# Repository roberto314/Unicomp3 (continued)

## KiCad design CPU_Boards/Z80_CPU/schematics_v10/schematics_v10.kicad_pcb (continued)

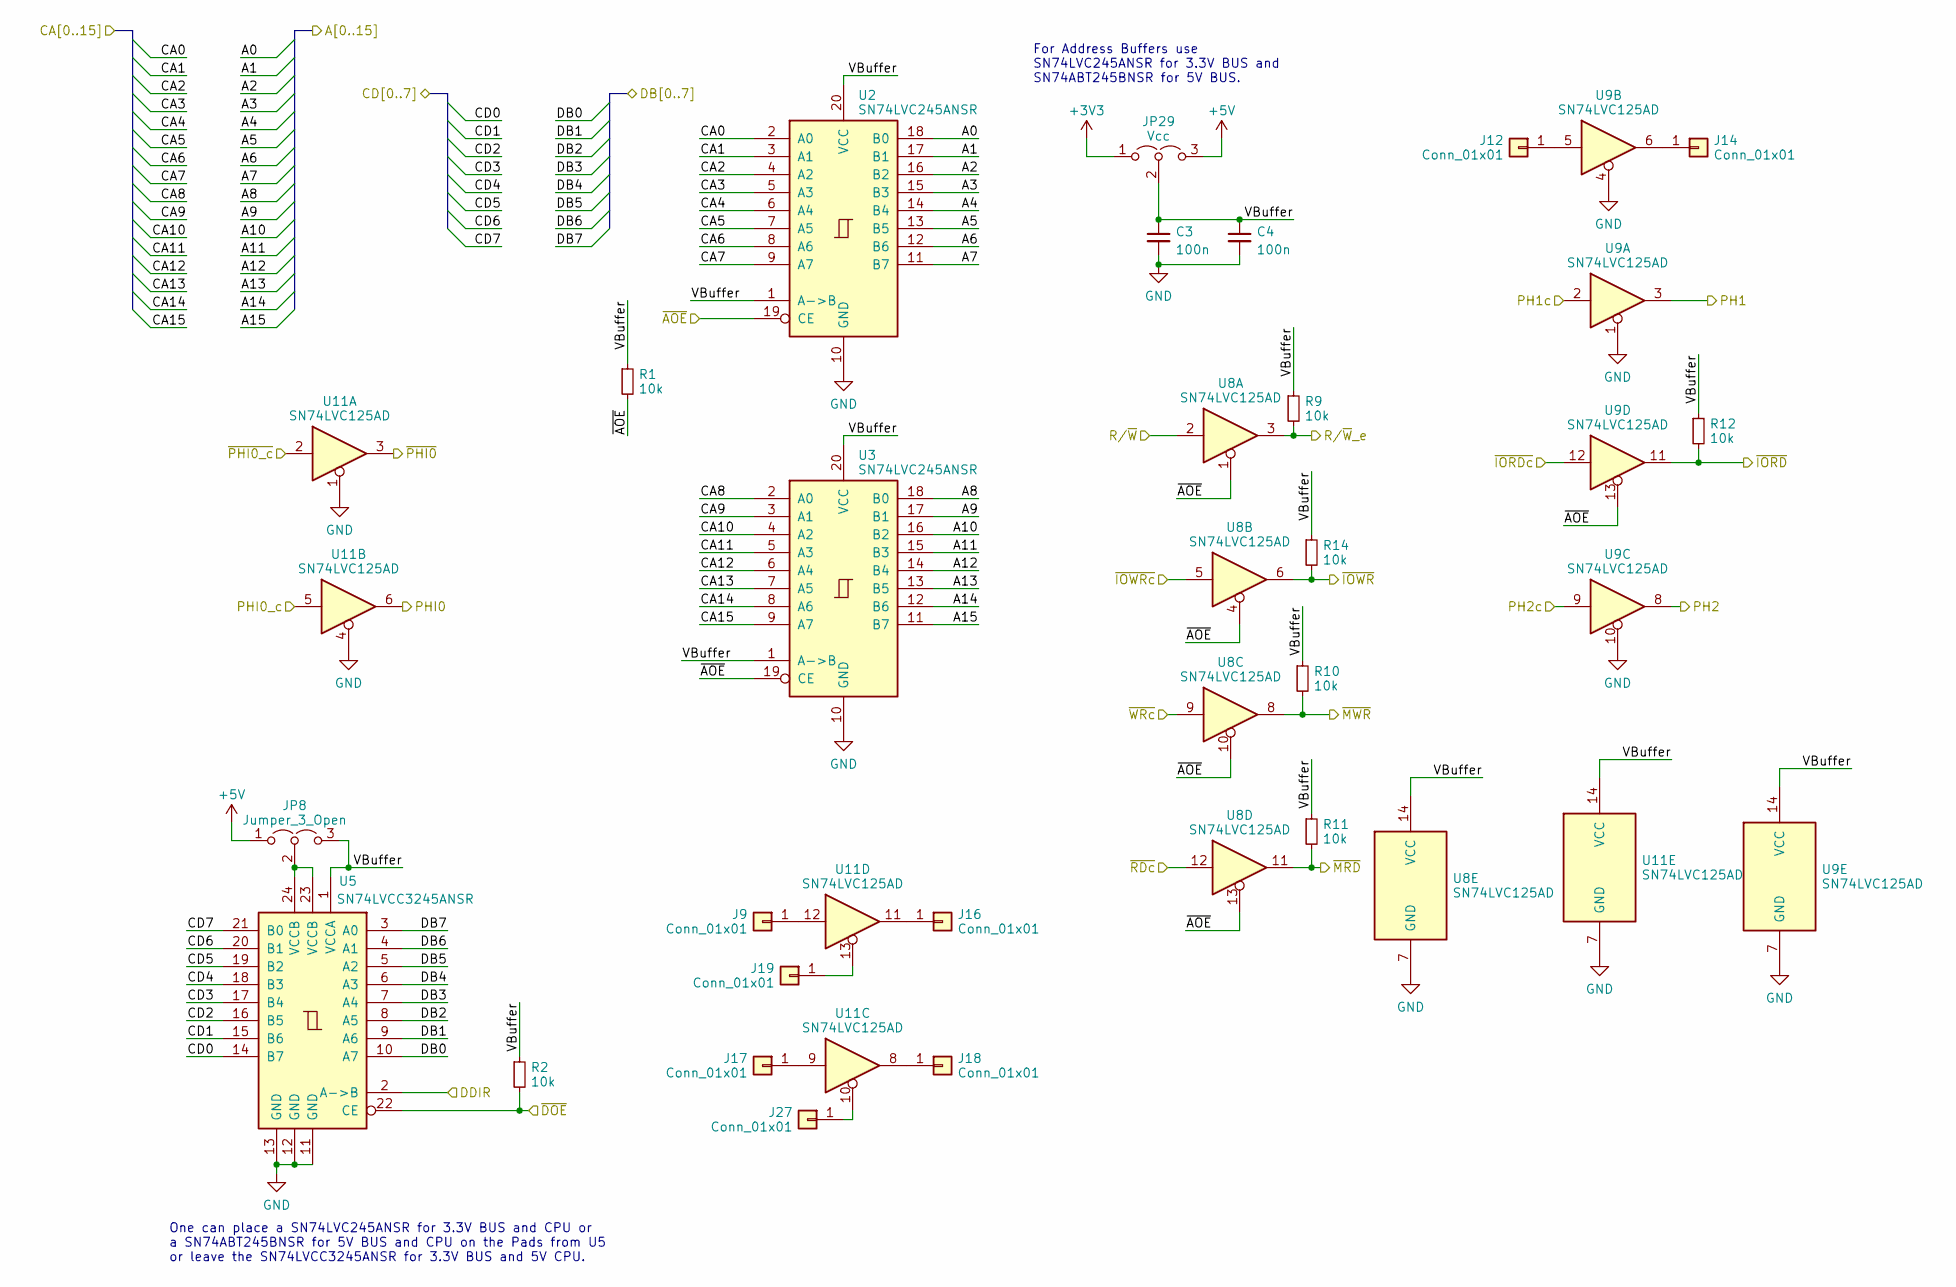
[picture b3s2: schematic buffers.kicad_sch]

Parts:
C3, C4: 100n; C_1206_3216Metric
J9, J12, J14, J16, J17, J18, J19, J27: Conn_01x01; PinHeader_1x01_P1.27mm_Vertical
JP8: Jumper_3_Open; SolderJumper-3_P1.3mm_Open_Pad1.0x1.5mm_NumberLabels
JP29: Vcc; SolderJumper-3_P1.3mm_Open_RoundedPad1.0x1.5mm_NumberLabels
R1, R2, R9, R10, R11, R12, R14: 10k; R_1206_3216Metric_Pad1.30x1.75mm_HandSolder
U2, U3: SN74LVC245ANSR; SO-20_5.3x12.6mm_P1.27mm
U5: SN74LVCC3245ANSR; SO-24_5.3x15mm_P1.27mm
U8, U9, U11: SN74LVC125AD; SOIC-14_3.9x8.7mm_P1.27mm

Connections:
+3V3: JP29.1 (A); also elsewhere on the board
+5V: JP8.1 (A), JP29.3 (B); also elsewhere on the board
/A0: U2.18 (B0); also elsewhere on the board
/A1: U2.17 (B1); also elsewhere on the board
/A2: U2.16 (B2); also elsewhere on the board
/A3: U2.15 (B3); also elsewhere on the board
/A4: U2.14 (B4); also elsewhere on the board
/A5: U2.13 (B5); also elsewhere on the board
/A6: U2.12 (B6); also elsewhere on the board
/A7: U2.11 (B7); also elsewhere on the board
/A8: U3.18 (B0); also elsewhere on the board
/A9: U3.17 (B1); also elsewhere on the board
/A10: U3.16 (B2); also elsewhere on the board
/A11: U3.15 (B3); also elsewhere on the board
/A12: U3.14 (B4); also elsewhere on the board
/A13: U3.13 (B5); also elsewhere on the board
/A14: U3.12 (B6); also elsewhere on the board
/A15: U3.11 (B7); also elsewhere on the board
/Buffers/R/~W: U8.2; also elsewhere on the board
/Buffers/VBuffer: C3.1, C4.1, JP8.3 (B), JP29.2 (C), R1.1, R2.1, R9.1, R10.1, R11.1, R12.1, R14.1, U2.1 (A->B), U2.20 (VCC), U3.1 (A->B), U3.20 (VCC), U5.1 (VCCA), U8.14 (VCC), U9.14 (VCC), U11.14 (VCC)
/CA0: U2.2 (A0); also elsewhere on the board
/CA1: U2.3 (A1); also elsewhere on the board
/CA2: U2.4 (A2); also elsewhere on the board
/CA3: U2.5 (A3); also elsewhere on the board
/CA4: U2.6 (A4); also elsewhere on the board
/CA5: U2.7 (A5); also elsewhere on the board
/CA6: U2.8 (A6); also elsewhere on the board
/CA7: U2.9 (A7); also elsewhere on the board
/CA8: U3.2 (A0); also elsewhere on the board
/CA9: U3.3 (A1); also elsewhere on the board
/CA10: U3.4 (A2); also elsewhere on the board
/CA11: U3.5 (A3); also elsewhere on the board
/CA12: U3.6 (A4); also elsewhere on the board
/CA13: U3.7 (A5); also elsewhere on the board
/CA14: U3.8 (A6); also elsewhere on the board
/CA15: U3.9 (A7); also elsewhere on the board
/CD0: U5.14 (B7); also elsewhere on the board
/CD1: U5.15 (B6); also elsewhere on the board
/CD2: U5.16 (B5); also elsewhere on the board
/CD3: U5.17 (B4); also elsewhere on the board
/CD4: U5.18 (B3); also elsewhere on the board
/CD5: U5.19 (B2); also elsewhere on the board
/CD6: U5.20 (B1); also elsewhere on the board
/CD7: U5.21 (B0); also elsewhere on the board
/DB0: U5.10 (A7); also elsewhere on the board
/DB1: U5.9 (A6); also elsewhere on the board
/DB2: U5.8 (A5); also elsewhere on the board
/DB3: U5.7 (A4); also elsewhere on the board
/DB4: U5.6 (A3); also elsewhere on the board
/DB5: U5.5 (A2); also elsewhere on the board
/DB6: U5.4 (A1); also elsewhere on the board
/DB7: U5.3 (A0); also elsewhere on the board
/DDIR: U5.2 (A->B); also elsewhere on the board
/PH1: U9.3; also elsewhere on the board
/PH1c: U9.2; also elsewhere on the board
/PH2: U9.8; also elsewhere on the board
/PH2c: U9.9; also elsewhere on the board
/PHI0: U11.6; also elsewhere on the board
/PHI0_c: U11.5; also elsewhere on the board
/R/~W_e: R9.2, U8.3; also elsewhere on the board
/ZZ3: U11.2; also elsewhere on the board
/ZZ5: R1.2, U2.19 (CE), U3.19 (CE), U8.1, U8.4, U8.10, U8.13, U9.13; also elsewhere on the board
/ZZ6: R2.2, U5.22 (CE); also elsewhere on the board
/ZZ8: U8.9; also elsewhere on the board
/ZZ12: U8.12; also elsewhere on the board
/ZZ13: U9.12; also elsewhere on the board
/ZZ16: U8.5; also elsewhere on the board
/~IORD: R12.2, U9.11; also elsewhere on the board
/~IOWR: R14.2, U8.6; also elsewhere on the board
/~MRD: R11.2, U8.11; also elsewhere on the board
/~MWR: R10.2, U8.8; also elsewhere on the board
/~PHI0: U11.3; also elsewhere on the board
GND: C3.2, C4.2, U2.10 (GND), U3.10 (GND), U5.11 (GND), U5.12 (GND), U5.13 (GND), U8.7 (GND), U9.1, U9.4, U9.7 (GND), U9.10, U11.1, U11.4, U11.7 (GND); also elsewhere on the board
unnamed: J9.1, U11.12
unnamed: J12.1, U9.5
unnamed: J14.1, U9.6
unnamed: J16.1, U11.11
unnamed: J17.1, U11.9
unnamed: J18.1, U11.8
unnamed: J19.1, U11.13
unnamed: J27.1, U11.10
unnamed: JP8.2 (C), U5.23 (VCCB), U5.24 (VCCB)

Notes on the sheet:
One can place a SN74LVC245ANSR for 3.3V BUS and CPU or a SN74ABT245BNSR for 5V BUS and CPU on the Pads from U5 or leave the SN74LVCC3245ANSR for 3.3V BUS and 5V CPU.
For Address Buffers use SN74LVC245ANSR for 3.3V BUS and SN74ABT245BNSR for 5V BUS.

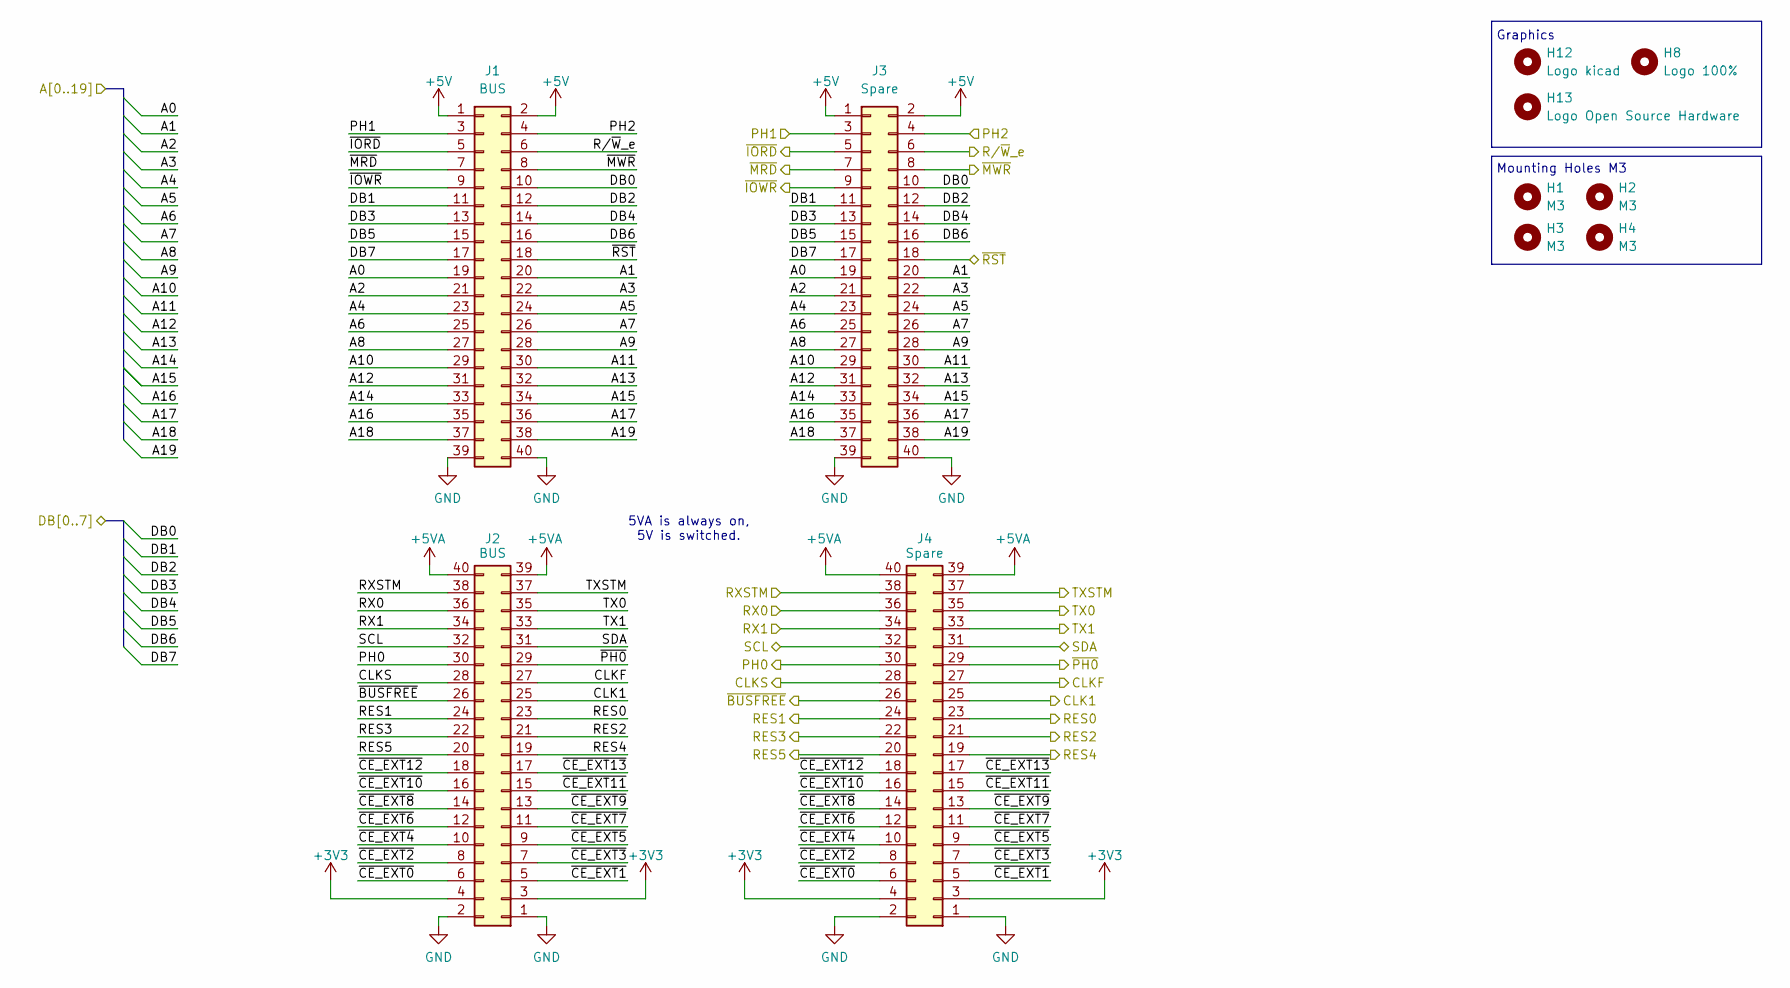
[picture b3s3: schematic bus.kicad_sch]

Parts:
H1, H2, H3, H4: M3; MountingHole_3.2mm_M3
H8: Logo 100%; Logo_100ProzentOffner_10x2.7mm
H12: Logo kicad; KiCad-Logo2_6mm_SilkScreen
H13: Logo Open Source Hardware; OSHW-Logo2_7.3x6mm_SilkScreen
J1, J2: BUS; PinSocket_2x20_P2.54mm_Vertical
J3, J4: Spare; PinSocket_2x20_P2.54mm_Vertical

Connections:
+3V3: J2.3, J2.4, J4.3, J4.4; also elsewhere on the board
+5V: J1.1, J1.2, J3.1, J3.2; also elsewhere on the board
+5VA: J2.39, J2.40, J4.39, J4.40; also elsewhere on the board
/A0: J1.19, J3.19; also elsewhere on the board
/A1: J1.20, J3.20; also elsewhere on the board
/A2: J1.21, J3.21; also elsewhere on the board
/A3: J1.22, J3.22; also elsewhere on the board
/A4: J1.23, J3.23; also elsewhere on the board
/A5: J1.24, J3.24; also elsewhere on the board
/A6: J1.25, J3.25; also elsewhere on the board
/A7: J1.26, J3.26; also elsewhere on the board
/A8: J1.27, J3.27; also elsewhere on the board
/A9: J1.28, J3.28; also elsewhere on the board
/A10: J1.29, J3.29; also elsewhere on the board
/A11: J1.30, J3.30; also elsewhere on the board
/A12: J1.31, J3.31; also elsewhere on the board
/A13: J1.32, J3.32; also elsewhere on the board
/A14: J1.33, J3.33; also elsewhere on the board
/A15: J1.34, J3.34; also elsewhere on the board
/Bus/A16: J1.35, J3.35
/Bus/A17: J1.36, J3.36
/Bus/A18: J1.37, J3.37
/Bus/A19: J1.38, J3.38
/Bus/CLK1: J2.25, J4.25
/Bus/RES2: J2.21, J4.21
/Bus/RES3: J2.22, J4.22
/Bus/RES4: J2.19, J4.19
/Bus/RES5: J2.20, J4.20
/Bus/RX0: J2.36, J4.36
/Bus/RX1: J2.34, J4.34
/Bus/RXSTM: J2.38, J4.38
/Bus/SCL: J2.32, J4.32
/Bus/SDA: J2.31, J4.31
/Bus/TX0: J2.35, J4.35
/Bus/TX1: J2.33, J4.33
/Bus/TXSTM: J2.37, J4.37
/Bus/~CE_EXT0: J2.6, J4.6
/Bus/~CE_EXT1: J2.5, J4.5
/Bus/~CE_EXT2: J2.8, J4.8
/Bus/~CE_EXT3: J2.7, J4.7
/Bus/~CE_EXT4: J2.10, J4.10
/Bus/~CE_EXT5: J2.9, J4.9
/Bus/~CE_EXT6: J2.12, J4.12
/Bus/~CE_EXT7: J2.11, J4.11
/Bus/~CE_EXT8: J2.14, J4.14
/Bus/~CE_EXT9: J2.13, J4.13
/Bus/~CE_EXT10: J2.16, J4.16
/Bus/~CE_EXT11: J2.15, J4.15
/Bus/~CE_EXT12: J2.18, J4.18
/Bus/~CE_EXT13: J2.17, J4.17
/CLKF: J2.27, J4.27; also elsewhere on the board
/CLKS: J2.28, J4.28
/DB0: J1.10, J3.10; also elsewhere on the board
/DB1: J1.11, J3.11; also elsewhere on the board
/DB2: J1.12, J3.12; also elsewhere on the board
/DB3: J1.13, J3.13; also elsewhere on the board
/DB4: J1.14, J3.14; also elsewhere on the board
/DB5: J1.15, J3.15; also elsewhere on the board
/DB6: J1.16, J3.16; also elsewhere on the board
/DB7: J1.17, J3.17; also elsewhere on the board
/PH1: J1.3, J3.3; also elsewhere on the board
/PH2: J1.4, J3.4; also elsewhere on the board
/PHI0: J2.30, J4.30; also elsewhere on the board
/RES0: J2.23, J4.23
/RES1: J2.24, J4.24
/R/~W_e: J1.6, J3.6; also elsewhere on the board
/ZZ43: J2.26, J4.26; also elsewhere on the board
/~IORD: J1.5, J3.5; also elsewhere on the board
/~IOWR: J1.9, J3.9; also elsewhere on the board
/~MRD: J1.7, J3.7; also elsewhere on the board
/~MWR: J1.8, J3.8; also elsewhere on the board
/~PHI0: J2.29, J4.29; also elsewhere on the board
/~RST: J1.18, J3.18; also elsewhere on the board
GND: J1.39, J1.40, J2.1, J2.2, J3.39, J3.40, J4.1, J4.2; also elsewhere on the board

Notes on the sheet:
5VA is always on, 5V is switched.
Graphics
Mounting Holes M3

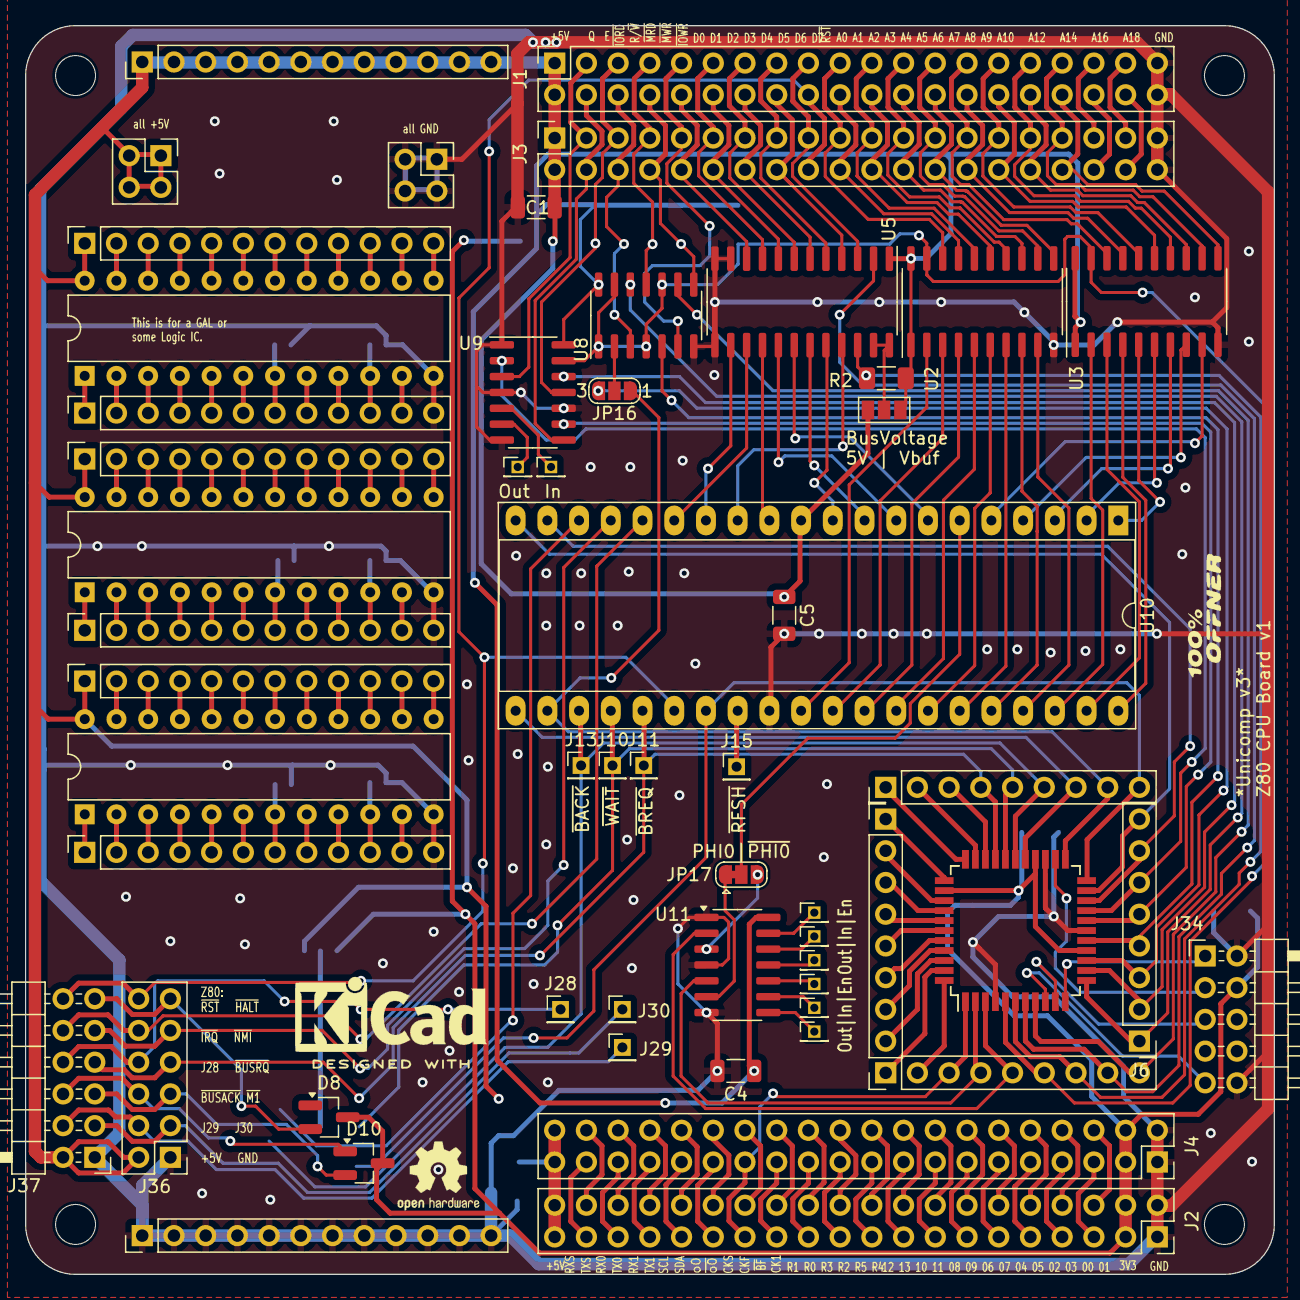
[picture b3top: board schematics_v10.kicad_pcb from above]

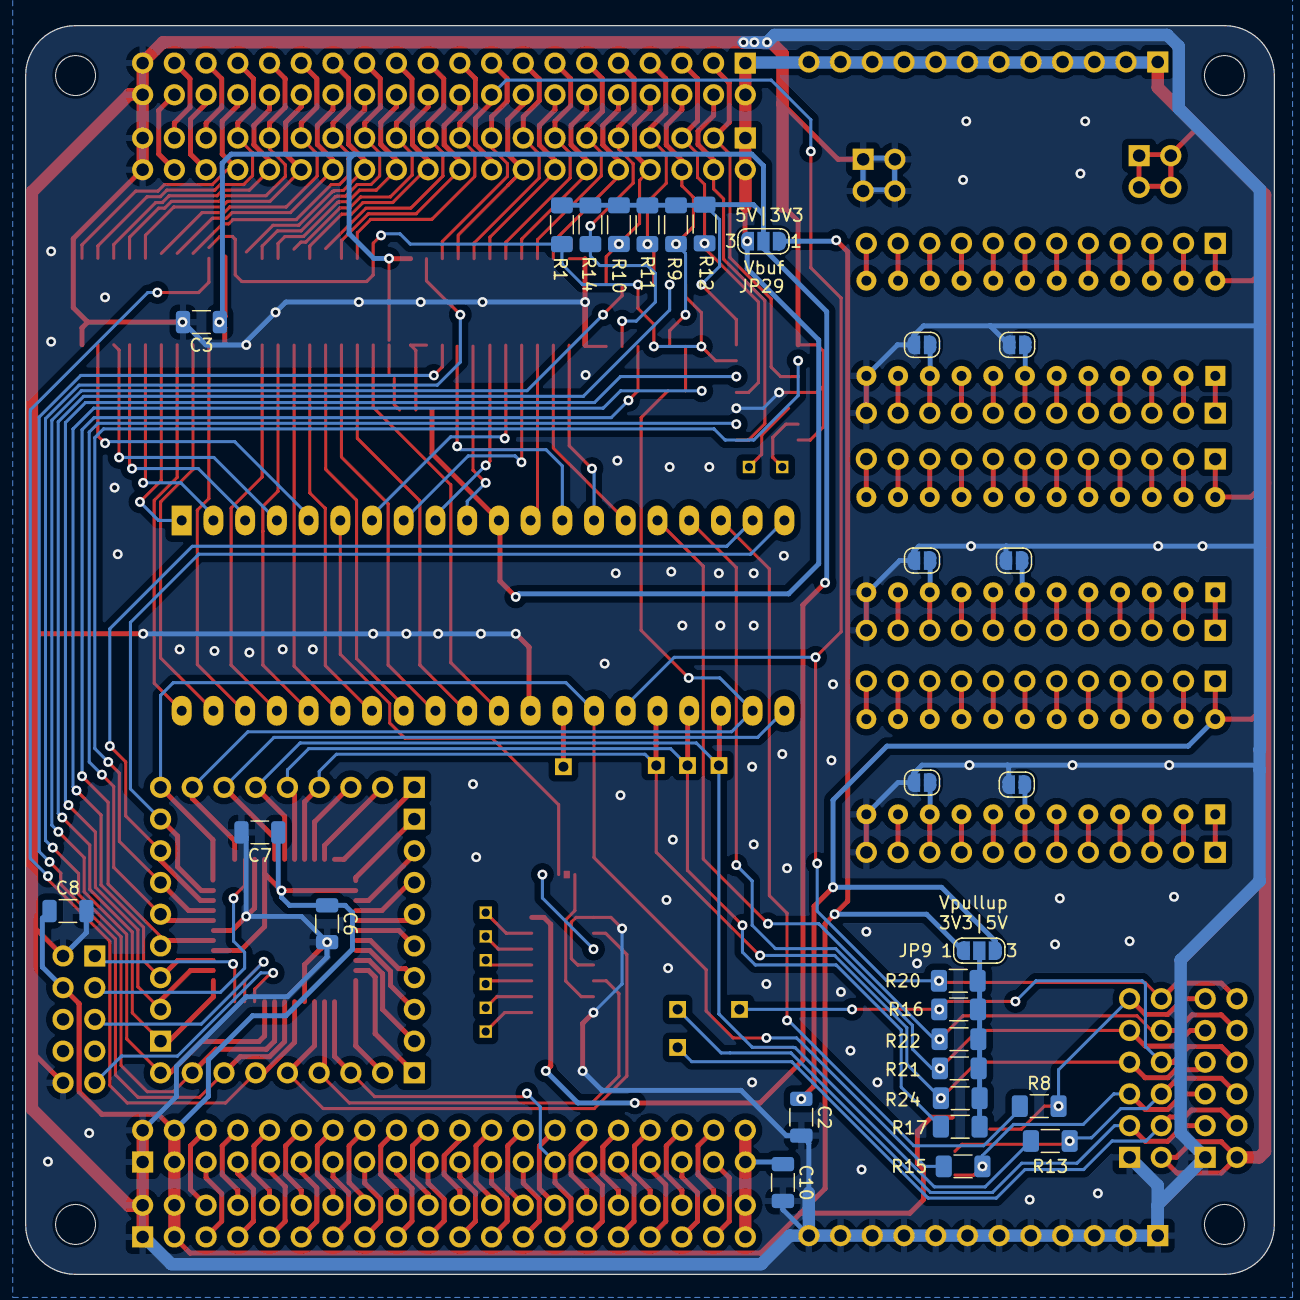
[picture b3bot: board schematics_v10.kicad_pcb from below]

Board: 2 copper layers, 100.0 x 100.0 mm, 92 parts (29 on the bottom side), 223 nets.

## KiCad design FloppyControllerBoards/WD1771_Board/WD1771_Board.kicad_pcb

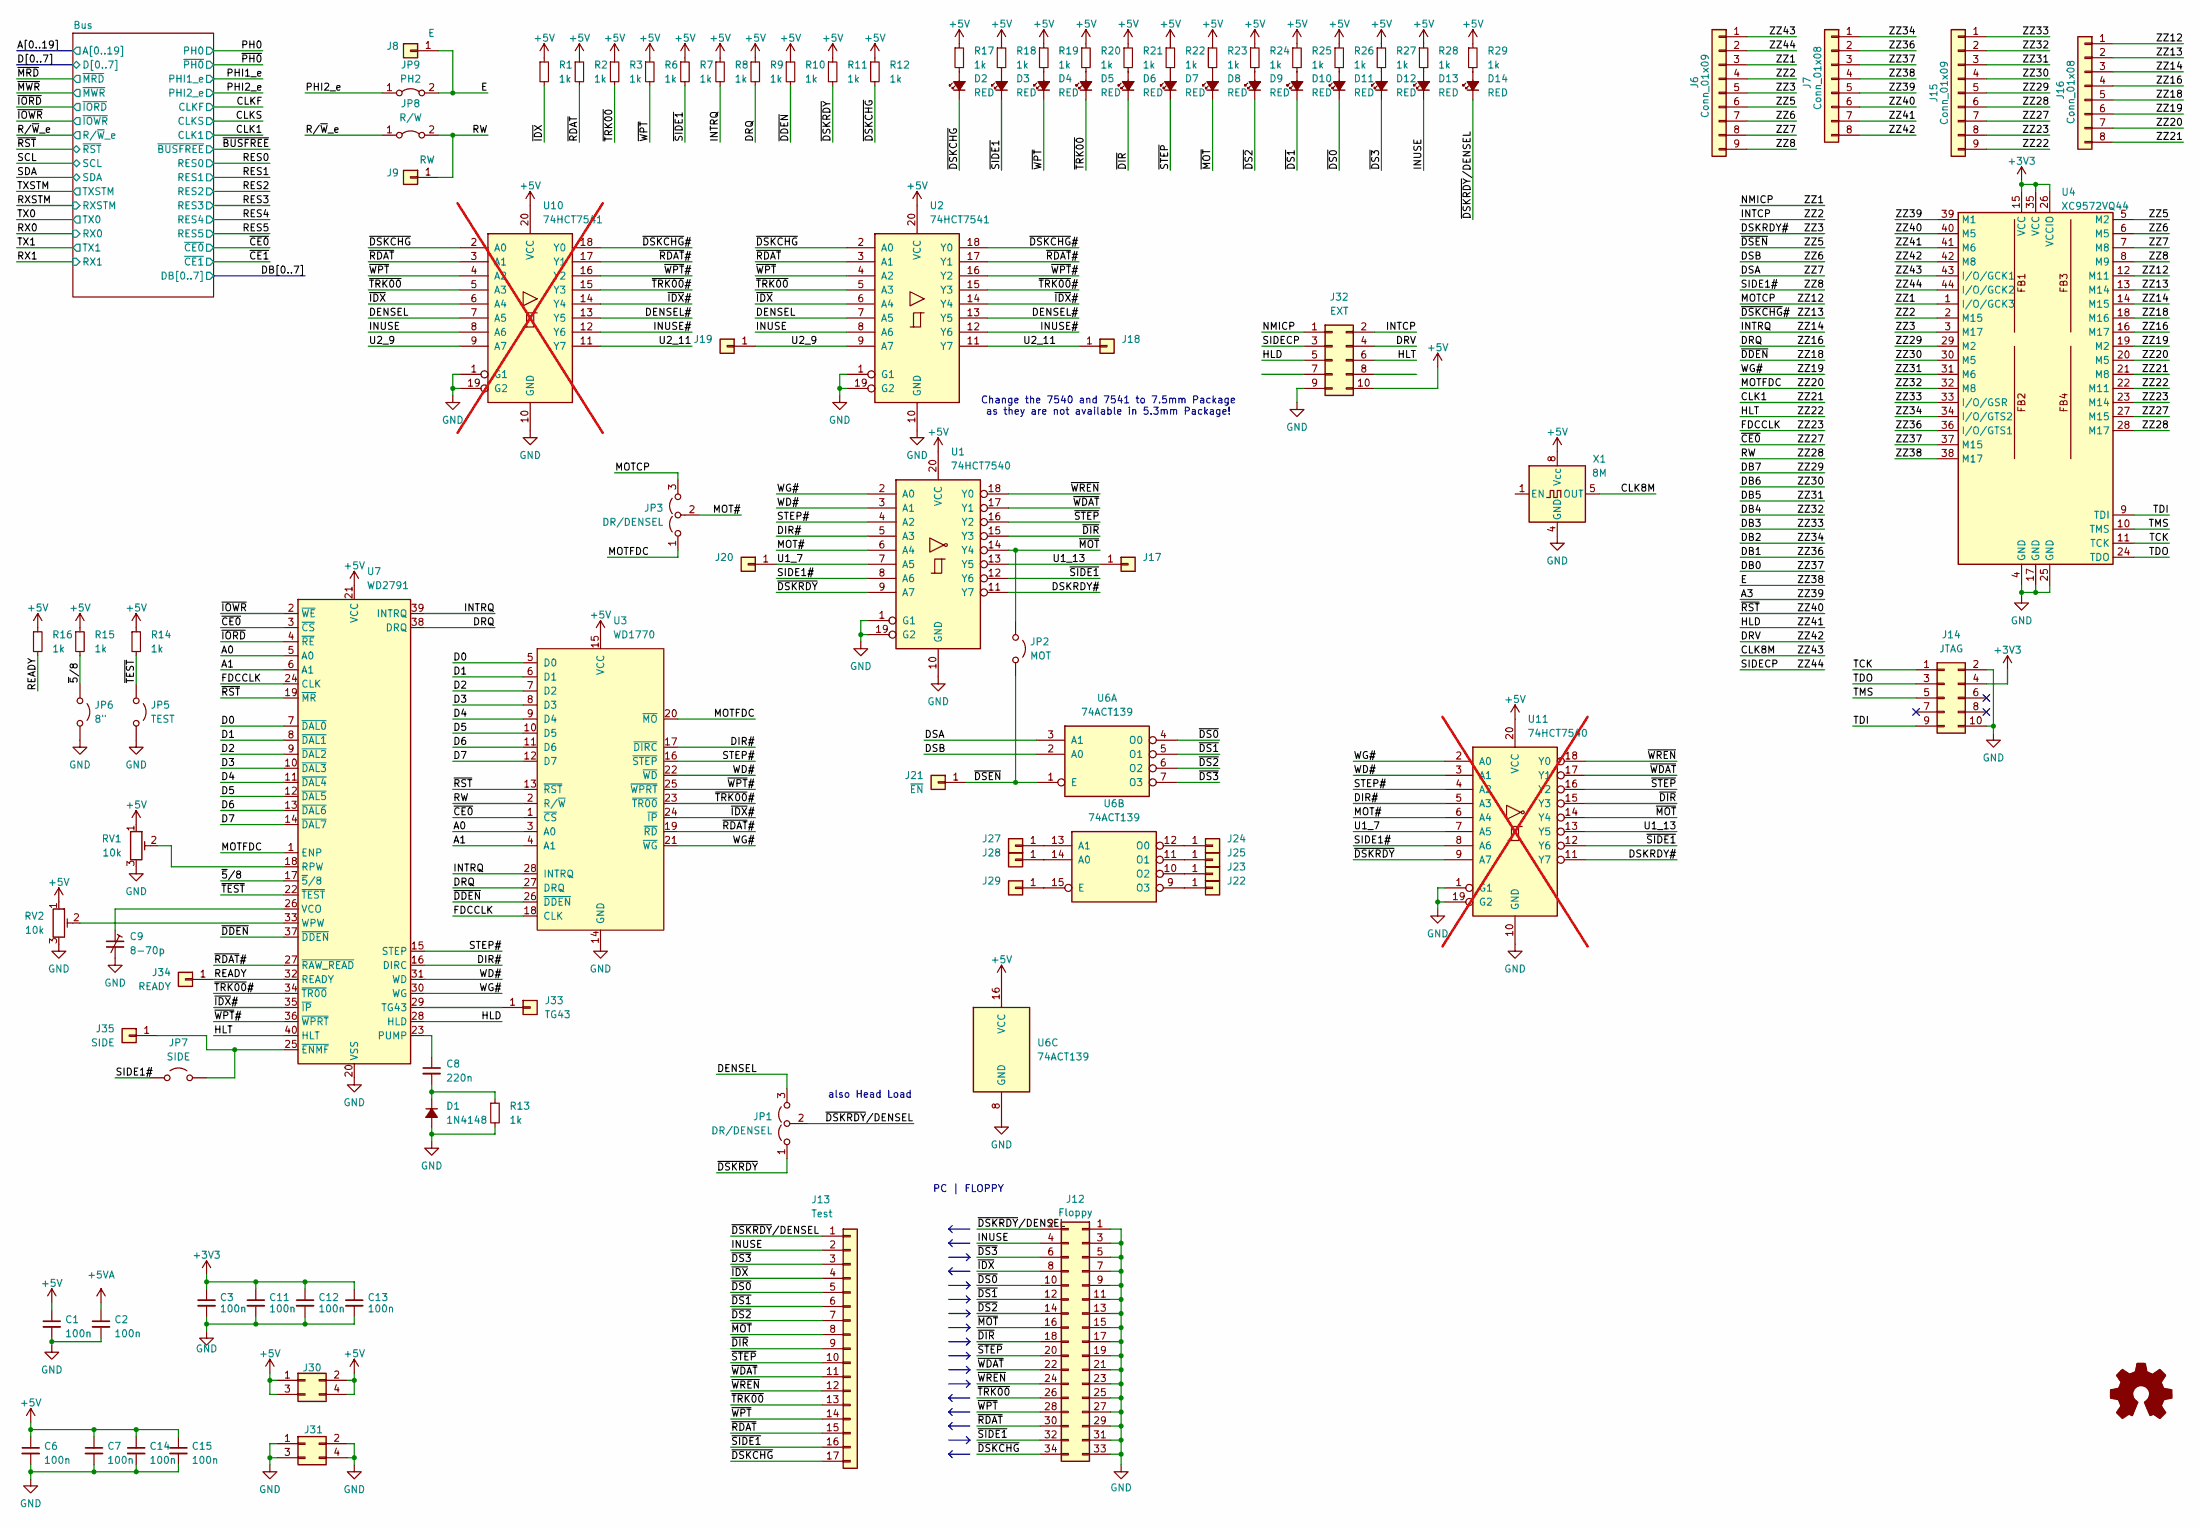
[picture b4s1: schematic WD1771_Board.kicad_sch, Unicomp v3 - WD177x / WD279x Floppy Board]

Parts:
C1, C2, C3, C6, C7, C11, C12, C13, C14, C15: 100n; C_1206_3216Metric
C8: 220n; C_1206_3216Metric
C9: 8-70p; Capacitor_Trim
D1: 1N4148; D_1206_3216Metric_Pad1.42x1.75mm_HandSolder
D2, D3, D4, D5, D6, D7, D8, D9, D10, D11, D12, D13, D14: RED; LED_1206_3216Metric_Pad1.42x1.75mm_HandSolder
J6, J15: Conn_01x09; PinHeader_1x09_P2.54mm_Vertical
J7, J16: Conn_01x08; PinHeader_1x08_P2.54mm_Vertical
J8: E; PinHeader_1x01_P2.00mm_Vertical
J9: RW; PinHeader_1x01_P2.00mm_Vertical
J12: Floppy; PinHeader_2x17_P2.54mm_Horizontal
J13: Test; PinSocket_1x17_P2.54mm_Vertical
J14: JTAG; PinHeader_2x05_P2.54mm_Horizontal
J17, J18, J19, J20, J22, J23, J24, J25, J27, J28, J29: Conn_01x01; PinHeader_1x01_P1.27mm_Vertical
J21: ~{EN}; PinHeader_1x01_P1.27mm_Vertical
J30, J31: Conn_02x02_Odd_Even; PinSocket_2x02_P2.54mm_Vertical
J32: EXT; PinHeader_2x05_P2.54mm_Horizontal
J33: TG43; PinHeader_1x01_P1.27mm_Vertical
J34: READY; PinHeader_1x01_P1.27mm_Vertical
J35: SIDE; PinHeader_1x01_P1.27mm_Vertical
JP1, JP3: DR/DENSEL; PinHeader_1x03_P2.54mm_Vertical
JP2: MOT; SolderJumper-2_P1.3mm_Open_RoundedPad1.0x1.5mm
JP5: TEST; SolderJumper-2_P1.3mm_Open_RoundedPad1.0x1.5mm
JP6: 8"; PinHeader_1x02_P2.54mm_Vertical
JP7: SIDE; SolderJumper-2_P1.3mm_Open_RoundedPad1.0x1.5mm
JP8: R/W; SolderJumper-2_P1.3mm_Bridged_RoundedPad1.0x1.5mm
JP9: PH2; SolderJumper-2_P1.3mm_Bridged_RoundedPad1.0x1.5mm
R1, R2, R3, R6, R7, R8, R9, R10, R11, R12, R13, R14, R15, R16, R17, R18, R19, R20, R21, R22, R23, R24, R25, R26, R27, R28, R29: 1k; R_1206_3216Metric_Pad1.30x1.75mm_HandSolder
RV1, RV2: 10k; Potentiometer_Vishay_T73XW_Horizontal
U1: 74HCT7540; SO-20_5.3x12.6mm_P1.27mm
U2: 74HCT7541; SO-20_5.3x12.6mm_P1.27mm
U3: WD1770; DIP-28_W15.24mm_Socket
U4: XC9572VQ44; TQFP-44_10x10mm_P0.8mm
U6: 74ACT139; SOIC-16_3.9x9.9mm_P1.27mm
U7: WD2791; DIP-40_W15.24mm
U10: 74HCT7541; SO-20_12.8x7.5mm_P1.27mm; not fitted
U11: 74HCT7540; SO-20_12.8x7.5mm_P1.27mm; not fitted
X1: 8M; Oscillator_DIP-8

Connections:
+3V3: C3.1, C11.1, C12.1, C13.1, J14.4, U4.15 (VCC), U4.26 (VCCIO), U4.35 (VCC); also elsewhere on the board
+5V: C1.1, C6.1, C7.1, C14.1, C15.1, J30.1, J30.2, J30.3, J30.4, J32.10, R1.1, R2.1, R3.1, R6.1, R7.1, R8.1, R9.1, R10.1, R11.1, R12.1, R14.1, R15.1, R16.1, R17.1, R18.1, R19.1, R20.1, R21.1, R22.1, R23.1, R24.1, R25.1, R26.1, R27.1, R28.1, R29.1, RV1.1, RV2.1, U1.20 (VCC), U2.20 (VCC), U3.15 (VCC), U6.16 (VCC), U7.21 (VCC), U10.20 (VCC), U11.20 (VCC), X1.8 (Vcc); also elsewhere on the board
+5VA: C2.1; also elsewhere on the board
/A0: U3.3 (A0), U7.5 (A0); also elsewhere on the board
/A1: U3.4 (A1), U7.6 (A1); also elsewhere on the board
/A3: J7.5, U4.39 (M1); also elsewhere on the board
/CLK1: J16.8, U4.21 (M8); also elsewhere on the board
/CLK8M: J6.1, U4.43 (I/O/GCK1), X1.5 (OUT)
/D0: U3.5 (D0), U7.7 (~DAL0); also elsewhere on the board
/D1: U3.6 (D1), U7.8 (~DAL1); also elsewhere on the board
/D2: U3.7 (D2), U7.9 (~DAL2); also elsewhere on the board
/D3: U3.8 (D3), U7.10 (~DAL3); also elsewhere on the board
/D4: U3.9 (D4), U7.11 (~DAL4); also elsewhere on the board
/D5: U3.10 (D5), U7.12 (~DAL5); also elsewhere on the board
/D6: U3.11 (D6), U7.13 (~DAL6); also elsewhere on the board
/D7: U3.12 (D7), U7.14 (~DAL7); also elsewhere on the board
/DB0: J7.3, U4.37 (M15); also elsewhere on the board
/DB1: J7.2, U4.36 (I/O/GTS1); also elsewhere on the board
/DB2: J7.1, U4.34 (I/O/GTS2); also elsewhere on the board
/DB3: J15.1, U4.33 (I/O/GSR); also elsewhere on the board
/DB4: J15.2, U4.32 (M8); also elsewhere on the board
/DB5: J15.3, U4.31 (M6); also elsewhere on the board
/DB6: J15.4, U4.30 (M5); also elsewhere on the board
/DB7: J15.5, U4.29 (M2); also elsewhere on the board
/DENSEL: JP1.3 (B), U2.7 (A5), U10.7 (A5)
/DENSEL#: U2.13 (Y5), U10.13 (Y5)
/DIR#: U1.5 (A3), U3.17 (~DIRC), U7.16 (DIRC), U11.5 (A3)
/DRQ: J16.4, R9.2, U3.27 (DRQ), U4.16 (M17), U7.38 (DRQ)
/DRV: J7.8, J32.4, U4.42 (M8)
/DSA: J6.8, U4.7 (M8), U6.3 (A1)
/DSB: J6.7, U4.6 (M5), U6.2 (A0)
/DSKRDY#: J6.5, U1.11 (Y7), U4.3 (M17), U11.11 (Y7)
/E: J7.4, J8.1, JP9.2 (B), U4.38 (M17)
/FDCCLK: J15.8, U3.18 (CLK), U4.23 (M14), U7.24 (CLK)
/HLD: J7.7, J32.5, U4.41 (M6), U7.28 (HLD)
/HLT: J15.9, J32.6, U4.22 (M11), U7.40 (HLT)
/INTCP: J6.4, J32.2, U4.2 (M15)
/INTRQ: J16.3, R8.2, U3.28 (INTRQ), U4.14 (M15), U7.39 (INTRQ)
/INUSE: D13.1 (K), J12.4, J13.2, U2.8 (A6), U10.8 (A6)
/INUSE#: U2.12 (Y6), U10.12 (Y6)
/MOT#: JP3.2 (C), U1.6 (A4), U11.6 (A4)
/MOTCP: J16.1, JP3.3 (B), U4.12 (M11)
/MOTFDC: J16.7, JP3.1 (A), U3.20 (~MO), U4.20 (M5), U7.1 (ENP)
/NMICP: J6.3, J32.1, U4.1 (I/O/GCK3)
/PHI2_e: JP9.1 (A); also elsewhere on the board
/READY: J34.1, R16.2, U7.32 (READY)
/RW: J9.1, J15.6, JP8.2 (B), U3.2 (R/~W), U4.28 (M17)
/R/~W_e: JP8.1 (A); also elsewhere on the board
/SIDE1#: J6.9, JP7.1 (A), U1.8 (A6), U4.8 (M9), U11.8 (A6)
/SIDECP: J6.2, J32.3, U4.44 (I/O/GCK2)
/STEP#: U1.4 (A2), U3.16 (~STEP), U7.15 (STEP), U11.4 (A2)
/TCK: J14.1, U4.11 (TCK)
/TDI: J14.9, U4.9 (TDI)
/TDO: J14.3, U4.24 (TDO)
/TMS: J14.5, U4.10 (TMS)
/U1_7: J20.1, U1.7 (A5), U11.7 (A5)
/U1_13: J17.1, U1.13 (Y5), U11.13 (Y5)
/U2_9: J19.1, U2.9 (A7), U10.9 (A7)
/U2_11: J18.1, U2.11 (Y7), U10.11 (Y7)
/WD#: U1.3 (A1), U3.22 (~WD), U7.31 (WD), U11.3 (A1)
/WG#: J16.6, U1.2 (A0), U3.21 (~WG), U4.19 (M2), U7.30 (WG), U11.2 (A0)
/ZZ5: J6.6, J21.1, JP2.2 (B), U4.5 (M2), U6.1 (E)
/ZZ13: J16.2, U2.18 (Y0), U4.13 (M14), U10.18 (Y0)
/ZZ18: J16.5, R10.2, U3.26 (~DDEN), U4.18 (M16), U7.37 (~DDEN)
/ZZ27: J15.7, U3.1 (~CS), U4.27 (M15), U7.3 (~CS); also elsewhere on the board
/ZZ40: J7.6, U3.13 (~RST), U4.40 (M5), U7.19 (~MR); also elsewhere on the board
/~5/8: JP6.1 (A), R15.2, U7.17 (~5/8)
/~DIR: D6.1 (K), J12.18, J13.9, U1.15 (Y3), U11.15 (Y3)
/~DS0: D11.1 (K), J12.10, J13.5, U6.4 (O0)
/~DS1: D10.1 (K), J12.12, J13.6, U6.5 (O1)
/~DS2: D9.1 (K), J12.14, J13.7, U6.6 (O2)
/~DS3: D12.1 (K), J12.6, J13.3, U6.7 (O3)
/~DSKCHG: D2.1 (K), J12.34, J13.17, R12.2, U2.2 (A0), U10.2 (A0)
/~DSKRDY: JP1.1 (A), R11.2, U1.9 (A7), U11.9 (A7)
/~DSKRDY/DENSEL: D14.1 (K), J12.2, J13.1, JP1.2 (C)
/~IDX: J12.8, J13.4, R1.2, U2.6 (A4), U10.6 (A4)
/~IDX#: U2.14 (Y4), U3.24 (~IP), U7.35 (~IP), U10.14 (Y4)
/~IORD: U7.4 (~RE); also elsewhere on the board
/~IOWR: U7.2 (~WE); also elsewhere on the board
/~MOT: D8.1 (K), J12.16, J13.8, JP2.1 (A), U1.14 (Y4), U11.14 (Y4)
/~RDAT: J12.30, J13.15, R2.2, U2.3 (A1), U10.3 (A1)
/~RDAT#: U2.17 (Y1), U3.19 (~RD), U7.27 (~RAW_READ), U10.17 (Y1)
/~SIDE1: D3.1 (K), J12.32, J13.16, R7.2, U1.12 (Y6), U11.12 (Y6)
/~STEP: D7.1 (K), J12.20, J13.10, U1.16 (Y2), U11.16 (Y2)
/~TEST: JP5.1 (A), R14.2, U7.22 (~TEST)
/~TRK00: D5.1 (K), J12.26, J13.13, R3.2, U2.5 (A3), U10.5 (A3)
/~TRK00#: U2.15 (Y3), U3.23 (~TR00), U7.34 (~TR00), U10.15 (Y3)
/~WDAT: J12.22, J13.11, U1.17 (Y1), U11.17 (Y1)
/~WPT: D4.1 (K), J12.28, J13.14, R6.2, U2.4 (A2), U10.4 (A2)
/~WPT#: U2.16 (Y2), U3.25 (~WPRT), U7.36 (~WPRT), U10.16 (Y2)
/~WREN: J12.24, J13.12, U1.18 (Y0), U11.18 (Y0)
GND: C1.2, C2.2, C3.2, C6.2, C7.2, C9.2, C11.2, C12.2, C13.2, C14.2, C15.2, D1.2 (A), J12.1, J12.3, J12.5, J12.7, J12.9, J12.11, J12.13, J12.15, J12.17, J12.19, J12.21, J12.23, J12.25, J12.27, J12.29, J12.31, J12.33, J14.2, J14.10, J31.1, J31.2, J31.3, J31.4, J32.9, JP5.2 (B), JP6.2 (B), R13.2, RV1.3, RV2.3, U1.1 (G1), U1.10 (GND), U1.19 (G2), U2.1 (G1), U2.10 (GND), U2.19 (G2), U3.14 (GND), U4.4 (GND), U4.17 (GND), U4.25 (GND), U6.8 (GND), U7.20 (VSS), U10.1 (G1), U10.10 (GND), U10.19 (G2), U11.1 (G1), U11.10 (GND), U11.19 (G2), X1.4 (GND); also elsewhere on the board
unnamed: C8.2, D1.1 (K), R13.1
unnamed: D2.2 (A), R17.2
unnamed: D3.2 (A), R18.2
unnamed: D4.2 (A), R19.2
unnamed: D5.2 (A), R20.2
unnamed: D6.2 (A), R21.2
unnamed: D7.2 (A), R22.2
unnamed: D8.2 (A), R23.2
unnamed: D9.2 (A), R24.2
unnamed: D10.2 (A), R25.2
unnamed: D11.2 (A), R26.2
unnamed: D12.2 (A), R27.2
unnamed: D13.2 (A), R28.2
unnamed: D14.2 (A), R29.2
unnamed: J22.1, U6.9 (O3)
unnamed: J23.1, U6.10 (O2)
unnamed: J24.1, U6.12 (O0)
unnamed: J25.1, U6.11 (O1)
unnamed: J27.1, U6.13 (A1)
unnamed: J28.1, U6.14 (A0)
unnamed: J29.1, U6.15 (E)
unnamed: J33.1, U7.29 (TG43)
unnamed: J35.1, JP7.2 (B), U7.25 (~ENMF)
unnamed: C8.1, U7.23 (PUMP)
unnamed: RV1.2, U7.18 (RPW)
unnamed: C9.1, U7.26 (VCO)
unnamed: RV2.2, U7.33 (WPW)

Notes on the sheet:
also Head Load
Change the 7540 and 7541 to 7.5mm Package as they are not available in 5.3mm Package!
PC | FLOPPY
